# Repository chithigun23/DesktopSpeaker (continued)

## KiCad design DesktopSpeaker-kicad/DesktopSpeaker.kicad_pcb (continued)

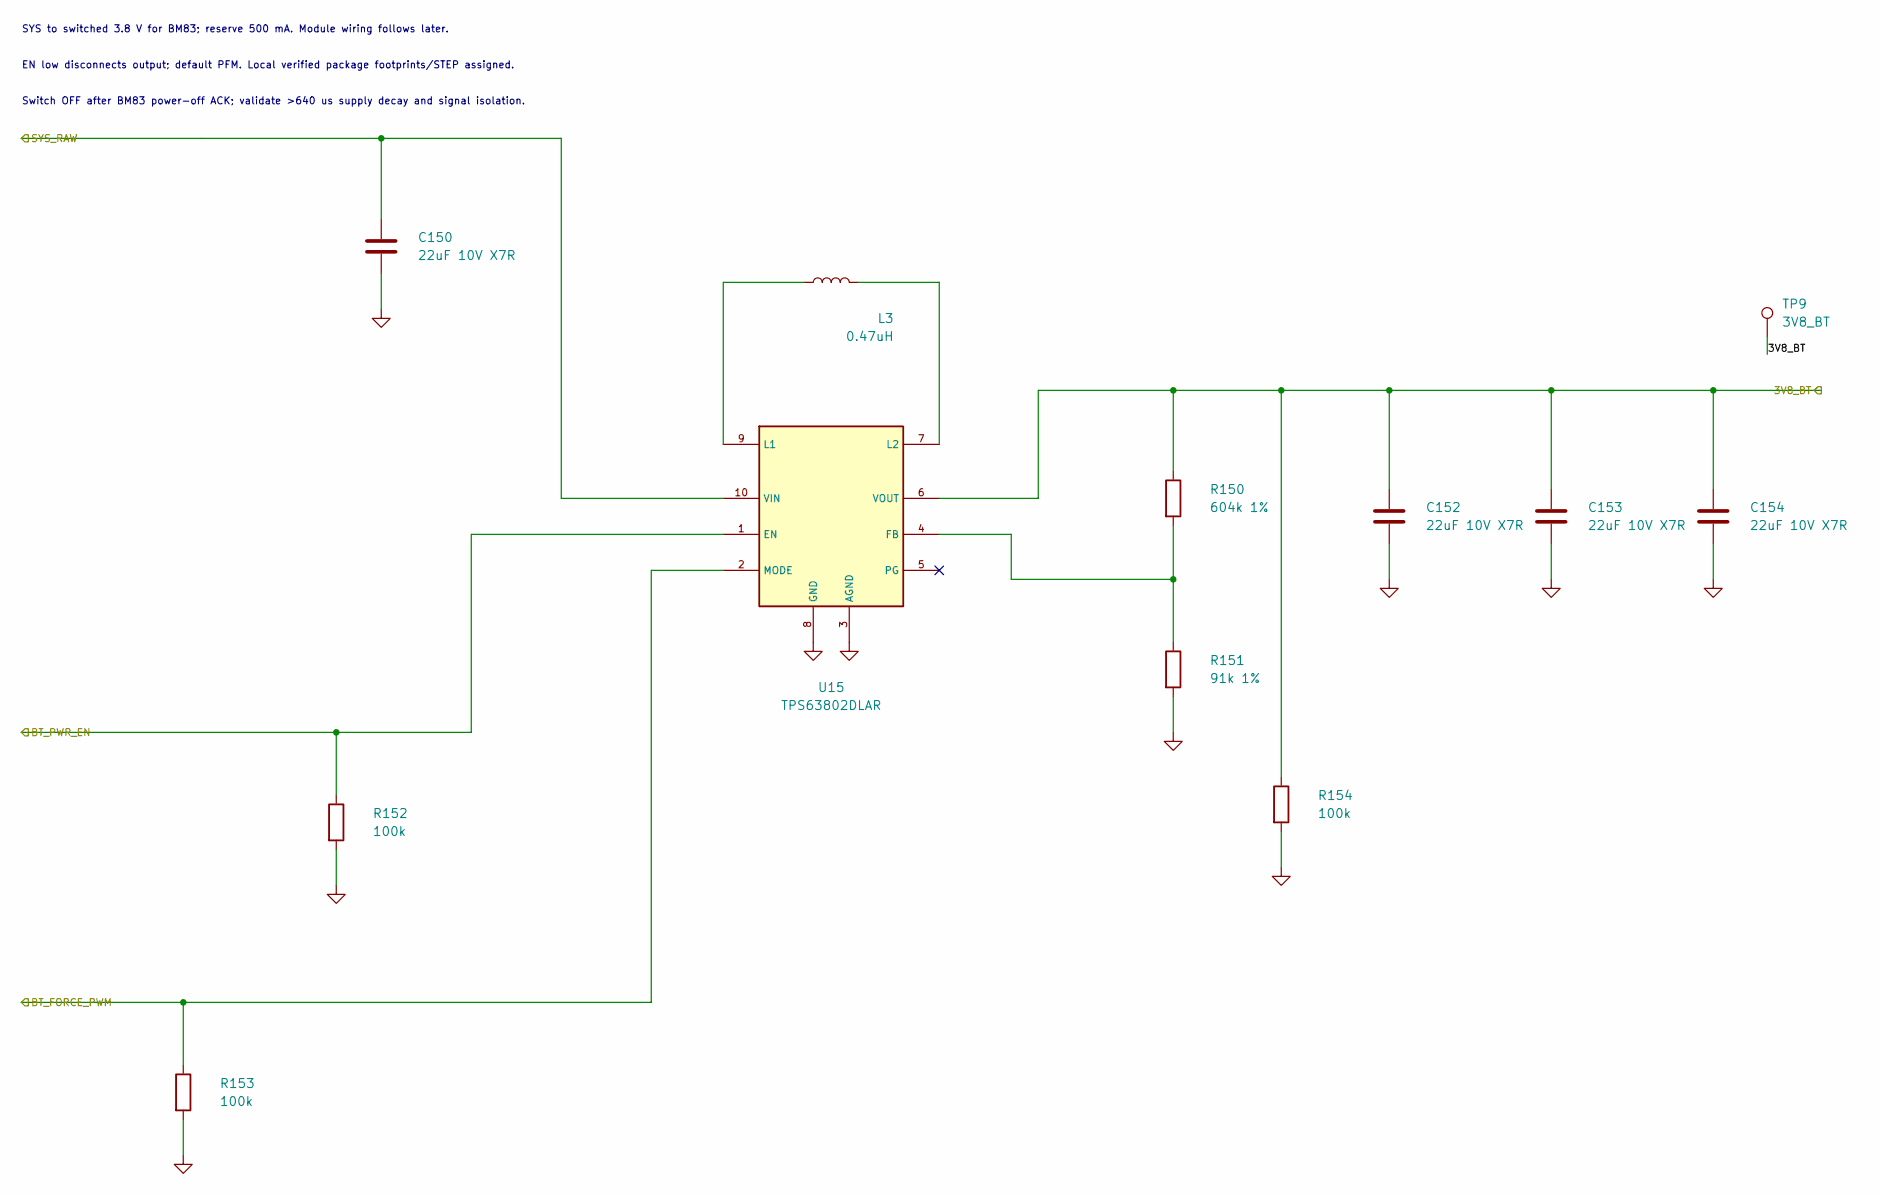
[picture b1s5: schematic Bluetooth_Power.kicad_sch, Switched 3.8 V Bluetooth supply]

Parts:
C150, C152, C153, C154: 22uF 10V X7R; C_0805_2012Metric_Pad1.18x1.45mm_HandSolder; MPN GRM21BZ71A226ME15L; LCSC C907991
L3: 0.47uH; Coilcraft_XFL4015-471MEC; MPN XFL4015-471MEC; LCSC Part C18221164
R150: 604k 1%; R_0402_1005Metric_Pad0.72x0.64mm_HandSolder; MPN 0402WGF6043TCE; LCSC C27013
R151: 91k 1%; R_0402_1005Metric_Pad0.72x0.64mm_HandSolder; MPN AC0402FR-0791KL; LCSC C144733
R152, R153, R154: 100k; R_0402_1005Metric_Pad0.72x0.64mm_HandSolder; MPN RC0402FR-07100KL; LCSC C60491
TP9: 3V8_BT; TestPoint_Keystone_5015_Micro_Mini
U15: TPS63802DLAR; MPN TPS63802DLAR; LCSC Part C2845237

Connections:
/3V8_BT: C152.1, C153.1, C154.1, R150.1, R154.1, TP9.1, U15.6 (VOUT); also elsewhere on the board
/BT_FORCE_PWM: R153.1, U15.2 (MODE); also elsewhere on the board
/BT_PWR_EN: R152.1, U15.1 (EN); also elsewhere on the board
/SYS_RAW: C150.1, U15.10 (VIN); also elsewhere on the board
GND: C150.2, C152.2, C153.2, C154.2, R151.2, R152.2, R153.2, R154.2, U15.3 (AGND), U15.8 (GND); also elsewhere on the board
unnamed: R150.2, R151.1, U15.4 (FB)
unnamed: L3.1, U15.9 (L1)
unnamed: L3.2, U15.7 (L2)

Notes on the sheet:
SYS to switched 3.8 V for BM83; reserve 500 mA. Module wiring follows later.
EN low disconnects output; default PFM. Local verified package footprints/STEP assigned.
Switch OFF after BM83 power-off ACK; validate >640 us supply decay and signal isolation.

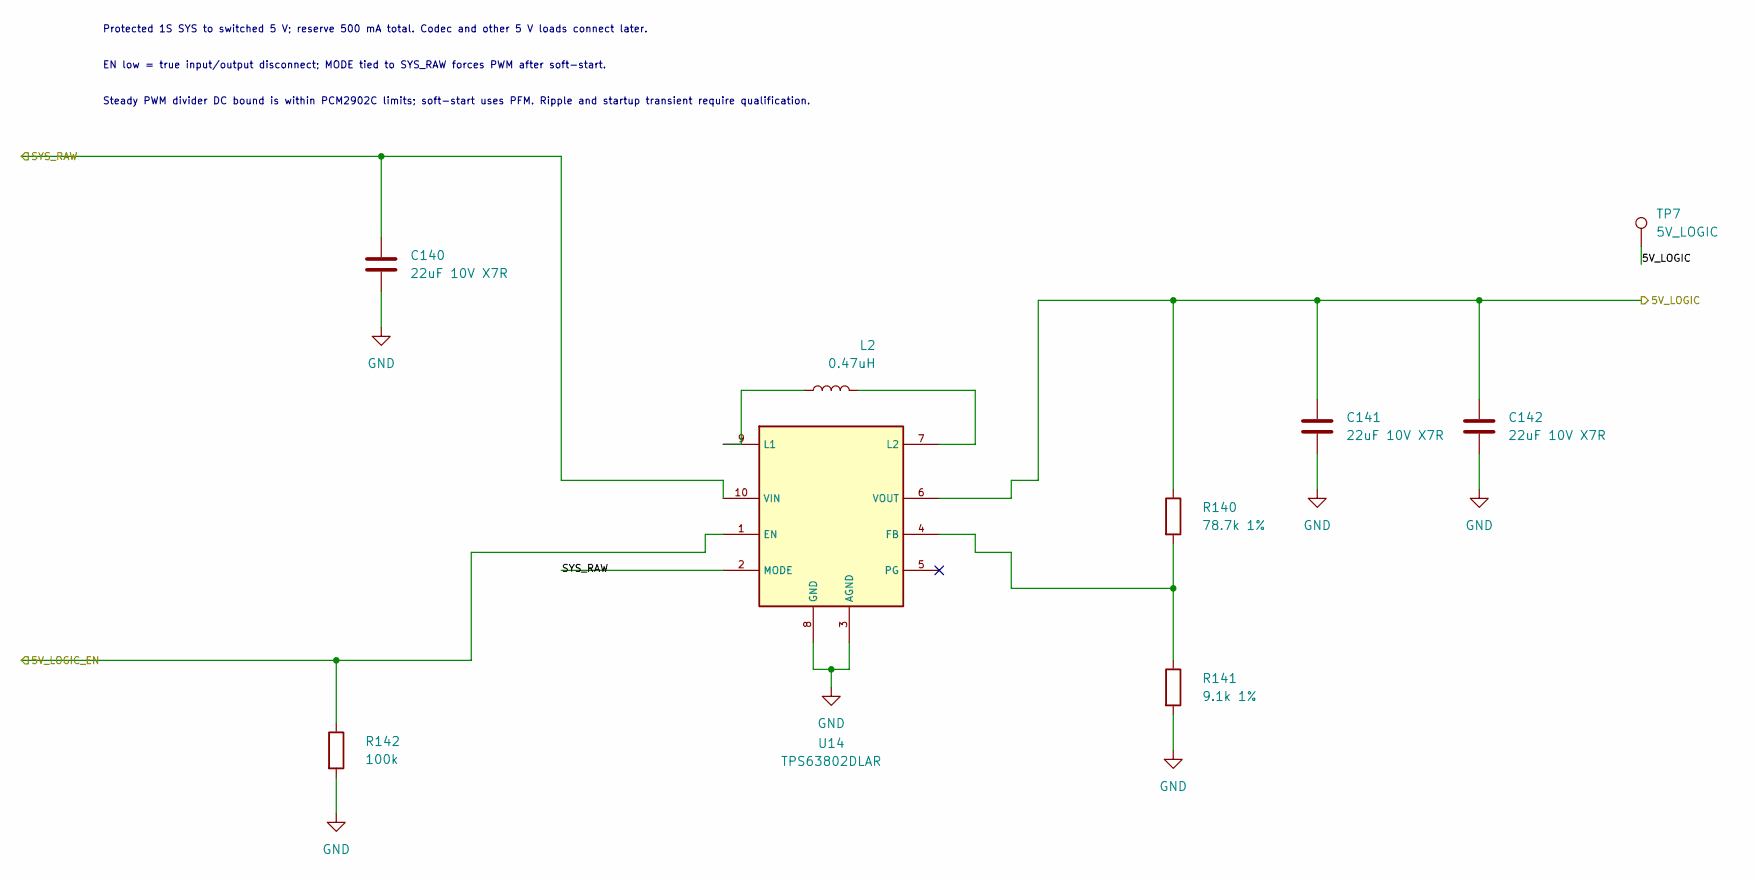
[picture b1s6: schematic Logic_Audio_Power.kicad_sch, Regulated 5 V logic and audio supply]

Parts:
C140, C141, C142: 22uF 10V X7R; C_0805_2012Metric_Pad1.18x1.45mm_HandSolder; MPN GRM21BZ71A226ME15L; LCSC C907991
L2: 0.47uH; Coilcraft_XFL4015-471MEC; MPN XFL4015-471MEC; LCSC Part C18221164
R140: 78.7k 1%; R_0402_1005Metric_Pad0.72x0.64mm_HandSolder; MPN RC0402FR-0778K7L; LCSC Part C163454
R141: 9.1k 1%; R_0402_1005Metric_Pad0.72x0.64mm_HandSolder; MPN RC0402FR-079K1L; LCSC Part C163450
R142: 100k; R_0402_1005Metric_Pad0.72x0.64mm_HandSolder; MPN RC0402FR-07100KL; LCSC Part C60491
TP7: 5V_LOGIC; TestPoint_Keystone_5015_Micro_Mini
U14: TPS63802DLAR; MPN TPS63802DLAR; LCSC Part C2845237

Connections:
/5V_LOGIC: C141.1, C142.1, R140.1, TP7.1, U14.6 (VOUT); also elsewhere on the board
/5V_LOGIC_EN: R142.1, U14.1 (EN); also elsewhere on the board
/SYS_RAW: C140.1, U14.2 (MODE), U14.10 (VIN); also elsewhere on the board
GND: C140.2, C141.2, C142.2, R141.2, R142.2, U14.3 (AGND), U14.8 (GND); also elsewhere on the board
unnamed: R140.2, R141.1, U14.4 (FB)
unnamed: L2.1, U14.9 (L1)
unnamed: L2.2, U14.7 (L2)

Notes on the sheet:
Protected 1S SYS to switched 5 V; reserve 500 mA total. Codec and other 5 V loads connect later.
EN low = true input/output disconnect; MODE tied to SYS_RAW forces PWM after soft-start.
Steady PWM divider DC bound is within PCM2902C limits; soft-start uses PFM. Ripple and startup transient require qualification.

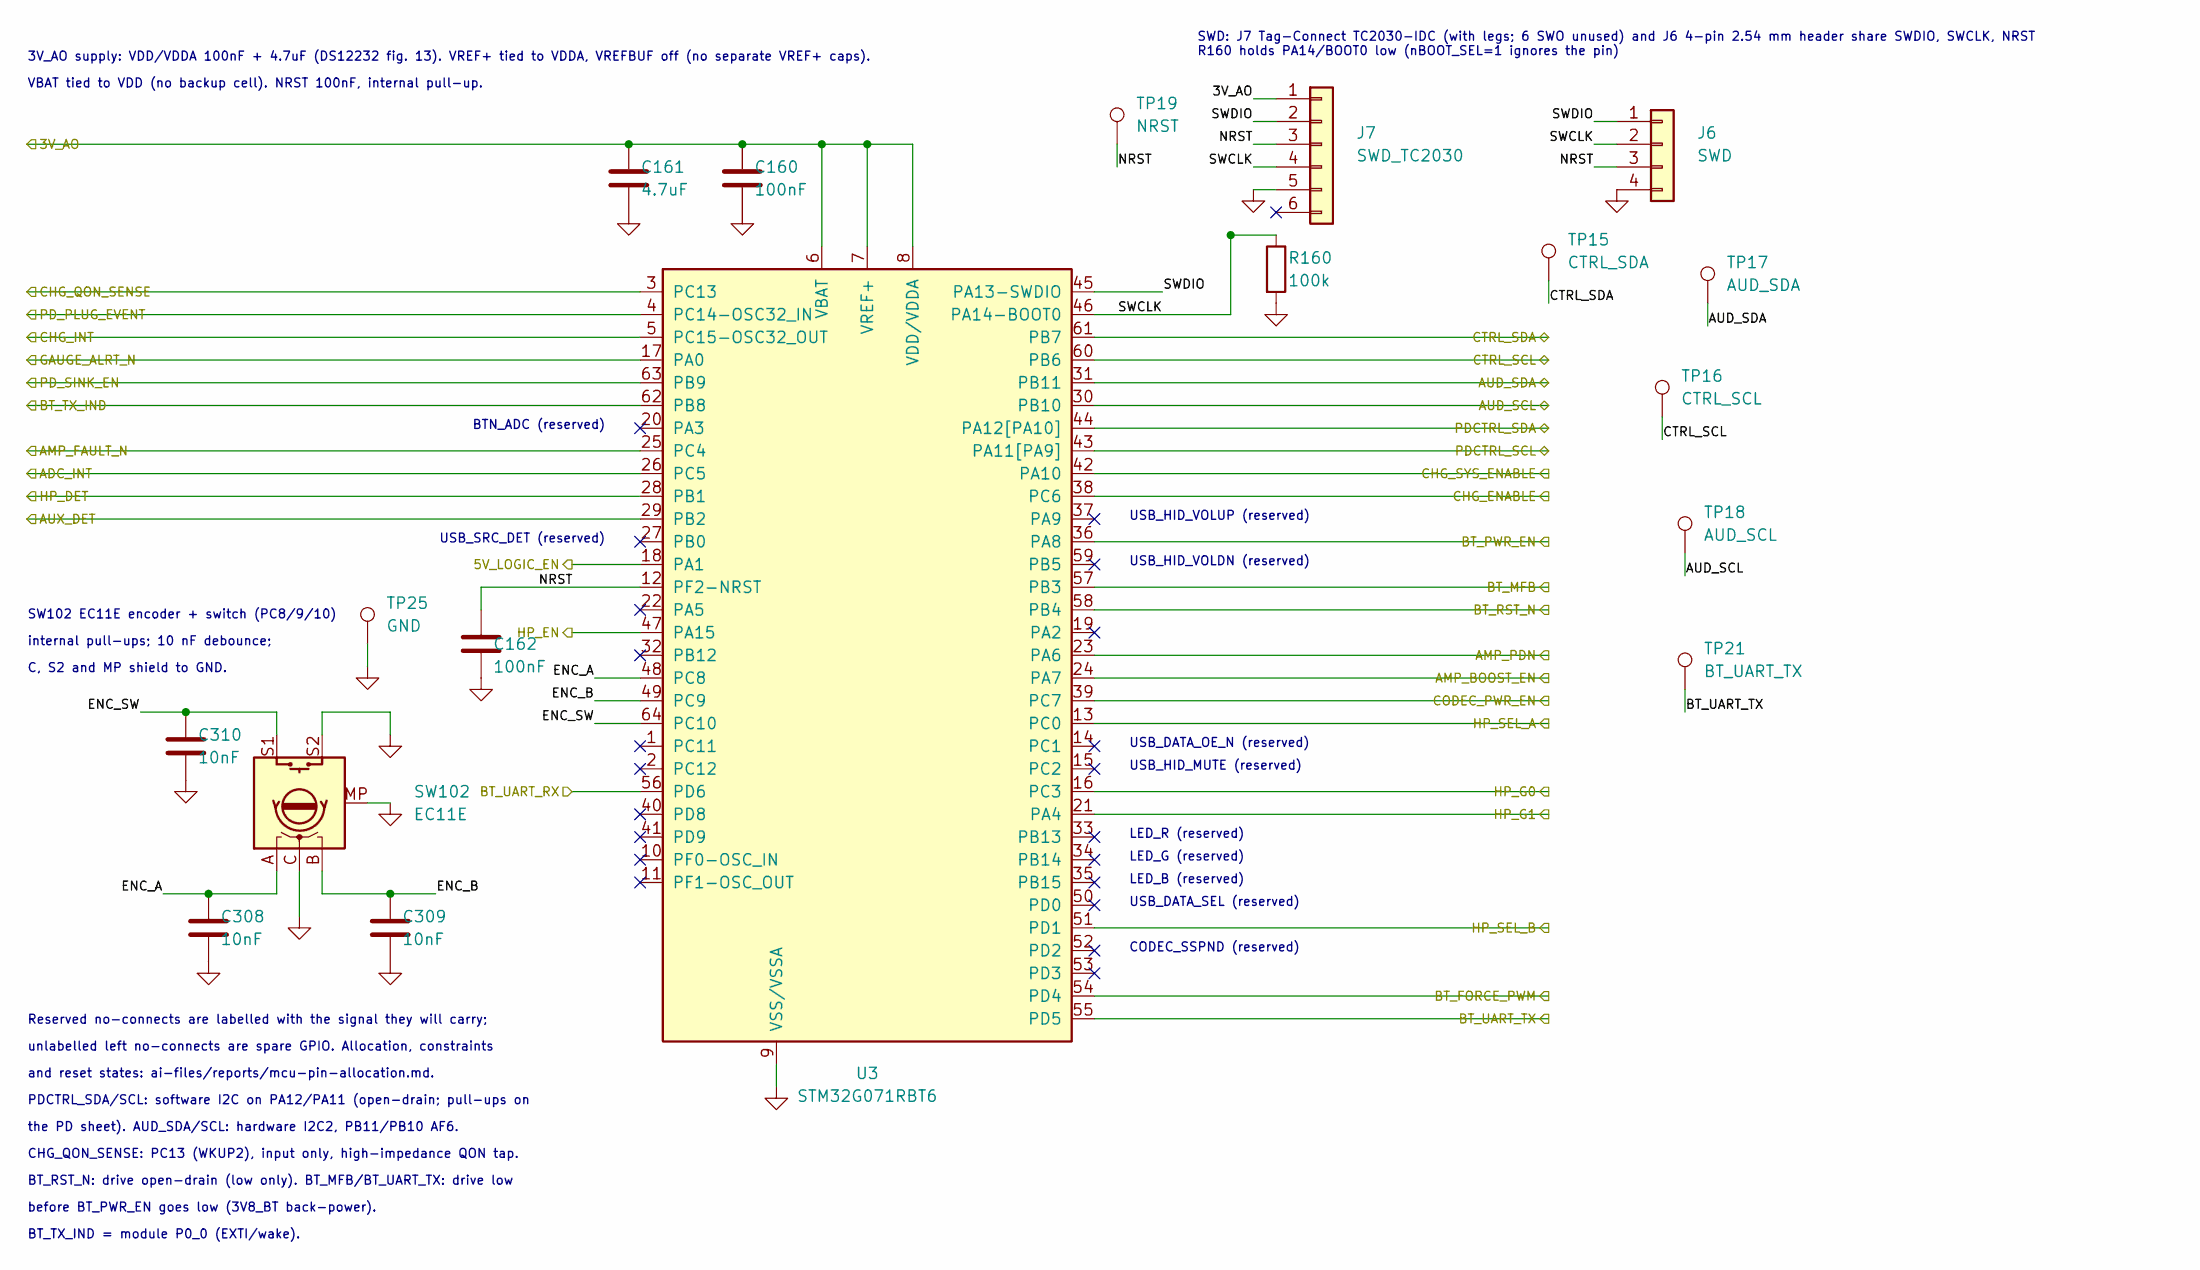
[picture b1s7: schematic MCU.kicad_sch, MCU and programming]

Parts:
C160, C162: 100nF; C_0402_1005Metric_Pad0.74x0.62mm_HandSolder; MPN GRM155R71H104KE14D; LCSC C77020
C161: 4.7uF; C_0805_2012Metric_Pad1.18x1.45mm_HandSolder; MPN CL21A475KAQNNNE; LCSC C1779
C308, C309, C310: 10nF; C_0402_1005Metric_Pad0.74x0.62mm_HandSolder; MPN GRM155R71H103KA88D; LCSC C77019
J6: SWD; PinHeader_1x04_P2.54mm_Vertical; MPN B-2100S04P-A110; LCSC C124378
J7: SWD_TC2030; Tag-Connect_TC2030-IDC-FP_2x03_P1.27mm_Vertical; MPN TC2030-IDC
R160: 100k; R_0402_1005Metric_Pad0.72x0.64mm_HandSolder; MPN RC0402FR-07100KL; LCSC C60491
SW102: EC11E; RotaryEncoder_Alps_EC11E-Switch_Vertical_H20mm_MountingHoles; MPN EC11E18244AU; LCSC C202365
TP15: CTRL_SDA; TestPoint_Keystone_5015_Micro_Mini
TP16: CTRL_SCL; TestPoint_Keystone_5015_Micro_Mini
TP17: AUD_SDA; TestPoint_Keystone_5015_Micro_Mini
TP18: AUD_SCL; TestPoint_Keystone_5015_Micro_Mini
TP19: NRST; TestPoint_Keystone_5015_Micro_Mini
TP21: BT_UART_TX; TestPoint_Keystone_5015_Micro_Mini
TP25: GND; TestPoint_Keystone_5010-5014_Multipurpose
U3: STM32G071RBT6; MPN STM32G071RBT6; LCSC Part C432213

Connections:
/3V_AO: C160.1, C161.1, J7.1, U3.6 (VBAT), U3.7 (VREF+), U3.8 (VDD/VDDA); also elsewhere on the board
/5V_LOGIC_EN: U3.18 (PA1); also elsewhere on the board
/ADC_INT: U3.26 (PC5); also elsewhere on the board
/AMP_BOOST_EN: U3.24 (PA7); also elsewhere on the board
/AMP_FAULT_N: U3.25 (PC4); also elsewhere on the board
/AMP_PDN: U3.23 (PA6); also elsewhere on the board
/AUD_SCL: TP18.1, U3.30 (PB10); also elsewhere on the board
/AUD_SDA: TP17.1, U3.31 (PB11); also elsewhere on the board
/AUX_DET: U3.29 (PB2); also elsewhere on the board
/BT_FORCE_PWM: U3.54 (PD4); also elsewhere on the board
/BT_MFB: U3.57 (PB3); also elsewhere on the board
/BT_PWR_EN: U3.36 (PA8); also elsewhere on the board
/BT_RST_N: U3.58 (PB4); also elsewhere on the board
/BT_TX_IND: U3.62 (PB8); also elsewhere on the board
/BT_UART_RX: U3.56 (PD6); also elsewhere on the board
/BT_UART_TX: TP21.1, U3.55 (PD5); also elsewhere on the board
/CHG_ENABLE: U3.38 (PC6); also elsewhere on the board
/CHG_INT: U3.5 (PC15-OSC32_OUT); also elsewhere on the board
/CHG_QON_SENSE: U3.3 (PC13); also elsewhere on the board
/CHG_SYS_ENABLE: U3.42 (PA10); also elsewhere on the board
/CODEC_PWR_EN: U3.39 (PC7); also elsewhere on the board
/CTRL_SCL: TP16.1, U3.60 (PB6); also elsewhere on the board
/CTRL_SDA: TP15.1, U3.61 (PB7); also elsewhere on the board
/GAUGE_ALRT_N: U3.17 (PA0); also elsewhere on the board
/HP_DET: U3.28 (PB1); also elsewhere on the board
/HP_EN: U3.47 (PA15); also elsewhere on the board
/HP_G0: U3.16 (PC3); also elsewhere on the board
/HP_G1: U3.21 (PA4); also elsewhere on the board
/HP_SEL_A: U3.13 (PC0); also elsewhere on the board
/HP_SEL_B: U3.51 (PD1); also elsewhere on the board
/MCU/ENC_A: C308.1, SW102.A, U3.48 (PC8)
/MCU/ENC_B: C309.1, SW102.B, U3.49 (PC9)
/MCU/ENC_SW: C310.1, SW102.S1, U3.64 (PC10)
/MCU/NRST: C162.1, J6.3, J7.3, TP19.1, U3.12 (PF2-NRST)
/MCU/SWCLK: J6.2, J7.4, R160.1, U3.46 (PA14-BOOT0)
/MCU/SWDIO: J6.1, J7.2, U3.45 (PA13-SWDIO)
/PDCTRL_SCL: U3.43 (PA11[PA9]); also elsewhere on the board
/PDCTRL_SDA: U3.44 (PA12[PA10]); also elsewhere on the board
/PD_PLUG_EVENT: U3.4 (PC14-OSC32_IN); also elsewhere on the board
/PD_SINK_EN: U3.63 (PB9); also elsewhere on the board
GND: C160.2, C161.2, C162.2, C308.2, C309.2, C310.2, J6.4, J7.5, R160.2, SW102.C, SW102.MP, SW102.S2, TP25.1, U3.9 (VSS/VSSA); also elsewhere on the board

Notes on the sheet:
SWD: J7 Tag-Connect TC2030-IDC (with legs; 6 SWO unused) and J6 4-pin 2.54 mm header share SWDIO, SWCLK, NRST R160 holds PA14/BOOT0 low (nBOOT_SEL=1 ignores the pin)
USB_SRC_DET (reserved)
BTN_ADC (reserved)
LED_R (reserved)
LED_G (reserved)
LED_B (reserved)
USB_DATA_SEL (reserved)
USB_DATA_OE_N (reserved)
CODEC_SSPND (reserved)
USB_HID_MUTE (reserved)
USB_HID_VOLUP (reserved)
USB_HID_VOLDN (reserved)
3V_AO supply: VDD/VDDA 100nF + 4.7uF (DS12232 fig. 13). VREF+ tied to VDDA, VREFBUF off (no separate VREF+ caps).
VBAT tied to VDD (no backup cell). NRST 100nF, internal pull-up.
Reserved no-connects are labelled with the signal they will carry;
unlabelled left no-connects are spare GPIO. Allocation, constraints
and reset states: ai-files/reports/mcu-pin-allocation.md.
PDCTRL_SDA/SCL: software I2C on PA12/PA11 (open-drain; pull-ups on
the PD sheet). AUD_SDA/SCL: hardware I2C2, PB11/PB10 AF6.
CHG_QON_SENSE: PC13 (WKUP2), input only, high-impedance QON tap.
BT_RST_N: drive open-drain (low only). BT_MFB/BT_UART_TX: drive low
before BT_PWR_EN goes low (3V8_BT back-power).
BT_TX_IND = module P0_0 (EXTI/wake).
SW102 EC11E encoder + switch (PC8/9/10)
internal pull-ups; 10 nF debounce;
C, S2 and MP shield to GND.

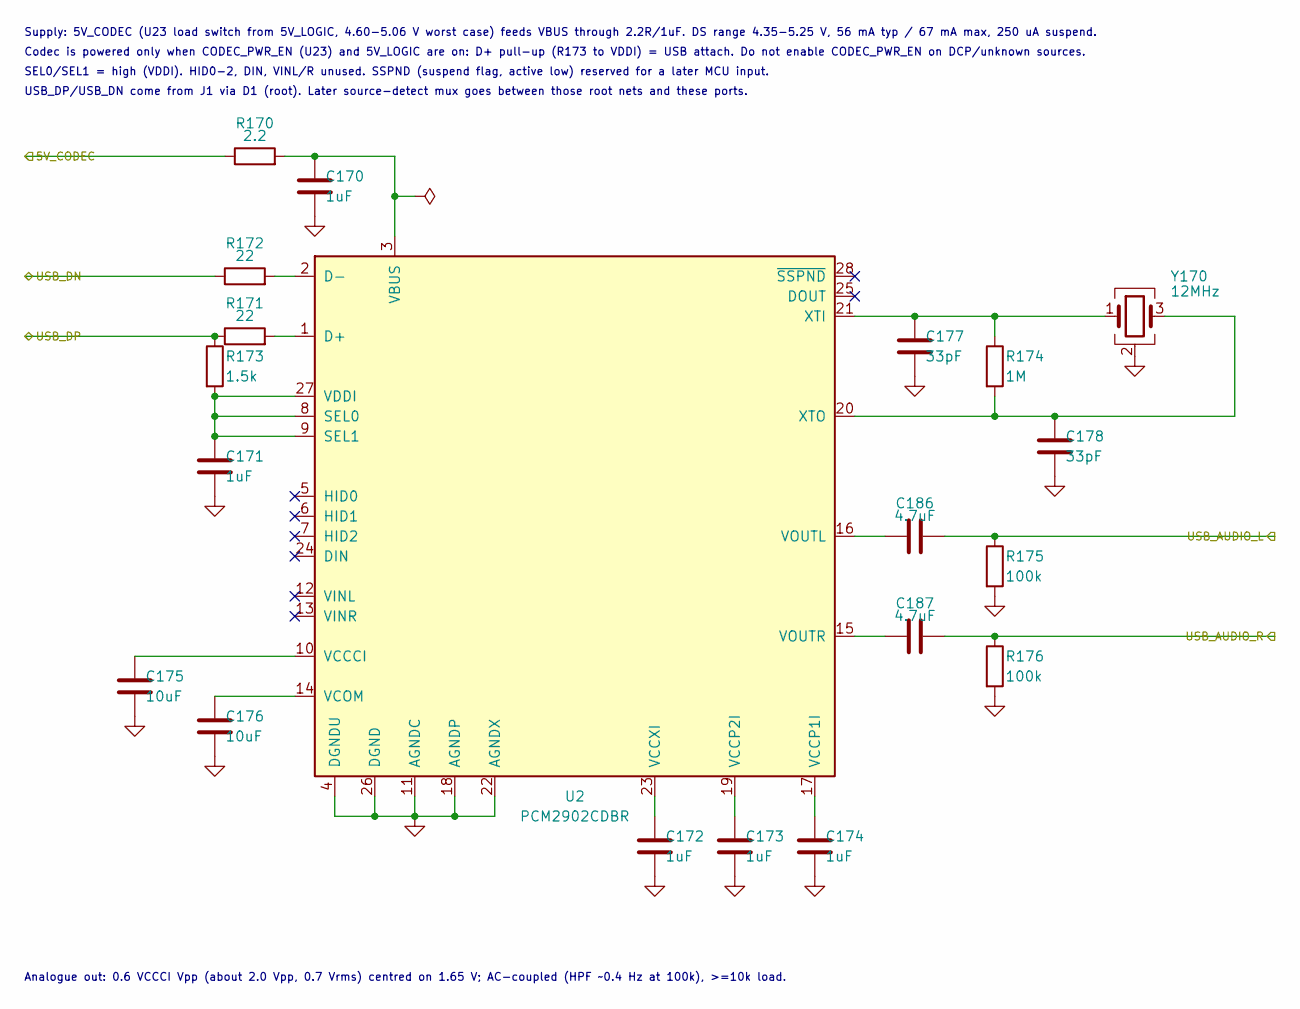
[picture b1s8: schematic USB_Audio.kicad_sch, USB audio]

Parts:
C170, C171, C172, C173, C174: 1uF; C_0402_1005Metric_Pad0.74x0.62mm_HandSolder; MPN CL05A105KO5NNNC; LCSC C29266
C175, C176: 10uF; C_0805_2012Metric_Pad1.18x1.45mm_HandSolder; MPN CL21B106KPQNNNE; LCSC C32635
C177, C178: 33pF; C_0402_1005Metric_Pad0.74x0.62mm_HandSolder; MPN FCC0402N330J500AT; LCSC C5137486
C186, C187: 4.7uF; C_0805_2012Metric_Pad1.18x1.45mm_HandSolder; MPN CL21A475KAQNNNE; LCSC C1779
R170: 2.2; R_0402_1005Metric_Pad0.72x0.64mm_HandSolder; MPN RC0402FR-072R2L; LCSC C327251
R171, R172: 22; R_0402_1005Metric_Pad0.72x0.64mm_HandSolder; MPN RC0402FR-0722RL; LCSC C114765
R173: 1.5k; R_0402_1005Metric_Pad0.72x0.64mm_HandSolder; MPN RC0402FR-071K5L; LCSC C114759
R174: 1M; R_0402_1005Metric_Pad0.72x0.64mm_HandSolder; MPN RC0402FR-071ML; LCSC C138033
R175, R176: 100k; R_0402_1005Metric_Pad0.72x0.64mm_HandSolder; MPN RC0402FR-07100KL; LCSC C60491
U2: PCM2902CDBR; MPN PCM2902CDBR; LCSC Part C2651869
Y170: 12MHz; Crystal_SMD_3225-4Pin_3.2x2.5mm; MPN K3A120002010; LCSC C368730

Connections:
/5V_CODEC: R170.1; also elsewhere on the board
/USB_AUDIO_L: C186.2, R175.1; also elsewhere on the board
/USB_AUDIO_R: C187.2, R176.1; also elsewhere on the board
/USB_DN: R172.1; also elsewhere on the board
/USB_DP: R171.1, R173.1; also elsewhere on the board
GND: C170.2, C171.2, C172.2, C173.2, C174.2, C175.2, C176.2, C177.2, C178.2, R175.2, R176.2, U2.4 (DGNDU), U2.11 (AGNDC), U2.18 (AGNDP), U2.22 (AGNDX), U2.26 (DGND), Y170.2 (G), Y170.4 (G); also elsewhere on the board
unnamed: R171.2, U2.1 (D+)
unnamed: R172.2, U2.2 (D-)
unnamed: C171.1, R173.2, U2.8 (SEL0), U2.9 (SEL1), U2.27 (VDDI)
unnamed: C170.1, R170.2, U2.3 (VBUS)
unnamed: C175.1, U2.10 (VCCCI)
unnamed: C174.1, U2.17 (VCCP1I)
unnamed: C173.1, U2.19 (VCCP2I)
unnamed: C172.1, U2.23 (VCCXI)
unnamed: C176.1, U2.14 (VCOM)
unnamed: C186.1, U2.16 (VOUTL)
unnamed: C187.1, U2.15 (VOUTR)
unnamed: C177.1, R174.1, U2.21 (XTI), Y170.1
unnamed: C178.1, R174.2, U2.20 (XTO), Y170.3

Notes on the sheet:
Supply: 5V_CODEC (U23 load switch from 5V_LOGIC, 4.60-5.06 V worst case) feeds VBUS through 2.2R/1uF. DS range 4.35-5.25 V, 56 mA typ / 67 mA max, 250 uA suspend.
Codec is powered only when CODEC_PWR_EN (U23) and 5V_LOGIC are on: D+ pull-up (R173 to VDDI) = USB attach. Do not enable CODEC_PWR_EN on DCP/unknown sources.
SEL0/SEL1 = high (VDDI). HID0-2, DIN, VINL/R unused. SSPND (suspend flag, active low) reserved for a later MCU input.
USB_DP/USB_DN come from J1 via D1 (root). Later source-detect mux goes between those root nets and these ports.
Analogue out: 0.6 VCCCI Vpp (about 2.0 Vpp, 0.7 Vrms) centred on 1.65 V; AC-coupled (HPF ~0.4 Hz at 100k), >=10k load.

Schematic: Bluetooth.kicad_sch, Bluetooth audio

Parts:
C190: 10uF; C_0805_2012Metric_Pad1.18x1.45mm_HandSolder; MPN CL21B106KPQNNNE; LCSC C32635
C191: 100nF; C_0402_1005Metric_Pad0.74x0.62mm_HandSolder; MPN GRM155R71H104KE14D; LCSC C77020
C192, C193: 1uF; C_0402_1005Metric_Pad0.74x0.62mm_HandSolder; MPN CL05A105KO5NNNC; LCSC C29266
C194, C195: 4.7uF; C_0805_2012Metric_Pad1.18x1.45mm_HandSolder; MPN CL21A475KAQNNNE
J8: BM83_PROG; PinHeader_1x05_P2.54mm_Vertical; MPN XY-MTP254-1X5; LCSC C54110162
R180, R181, R184: 100k; R_0402_1005Metric_Pad0.72x0.64mm_HandSolder; MPN RC0402FR-07100KL; LCSC C60491
R182, R183: 10k; R_0402_1005Metric_Pad0.72x0.64mm_HandSolder; MPN RC0402FR-0710KL; LCSC C60490
R185, R186, R187: 1k; R_0402_1005Metric_Pad0.72x0.64mm_HandSolder; MPN RC0402FR-071KL
TP22: BT_UART_RX; TestPoint_Keystone_5015_Micro_Mini
U1: BM83SM1-00TA; MPN BM83SM1-00TA; LCSC Part C6752723

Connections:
/3V8_BT: C190.1, C191.1, U1.23 (BAT_IN); also elsewhere on the board
/BT_AUDIO_L: C194.2, R180.1; also elsewhere on the board
/BT_AUDIO_R: C195.2, R181.1; also elsewhere on the board
/BT_MFB: R183.1; also elsewhere on the board
/BT_RST_N: R185.1; also elsewhere on the board
/BT_TX_IND: R187.2; also elsewhere on the board
/BT_UART_RX: R186.2, TP22.1; also elsewhere on the board
/BT_UART_TX: R182.1; also elsewhere on the board
/Bluetooth/BT_RST_M: J8.1, R185.2, U1.43 (RST_N)
/Bluetooth/BT_RXD_M: J8.3, R182.2, U1.29 (P8_6/UART_RXD)
/Bluetooth/BT_SYS_CFG: J8.2, U1.31 (P3_4/UART_RTS)
/Bluetooth/BT_TXD_M: J8.4, R186.1, U1.30 (P8_5/UART_TXD)
GND: C190.2, C191.2, C192.2, C193.2, J8.5, R180.2, R181.2, R184.2, U1.16, U1.50, U1.56, U1.57, U1.[16,50,56,57] (GND); also elsewhere on the board
unnamed: C194.1, U1.8 (AOHPL)
unnamed: C195.1, U1.6 (AOHPR)
unnamed: R187.1, U1.49 (P0_0/UART_TX_IND)
unnamed: R183.2, R184.1, U1.26 (PWR(MFB))
unnamed: C193.1, U1.24 (SYS_PWR)
unnamed: C192.1, U1.25 (VDD_IO)

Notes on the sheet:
BM83SM1-00TA (DS70005402D). BAT_IN 3.2-4.2 V from 3V8_BT (U15); SYS_PWR/VDD_IO are outputs (decoupling only, do not load or feed). ADAP_IN unused (internal charger/USB DFU not used).
Host mode UART from the MCU: P8_6 RXD / P8_5 TXD, P0_0 = UART_TX_IND (wakes the MCU). MFB (PWR) = power-on/wake key, RST_N = reset (active low, internal pull-up). Config Tool must set Host mode, P0_0 as TX_IND.
Back-power: MCU lines pass 10k/1k series resistors; firmware must drive PA2/PB3 low (PB4 open-drain/hi-Z) and disable BT_PWR_EN only after the module power-off ACK. Module outputs are 3.0-3.6 V into 5 V tolerant MCU pins.
Audio: single-ended DAC out (AOHPL/AOHPR) AC-coupled, 4.7 uF + 100k bleed, 0.74 Vrms full scale; AOHPM (capless sense) unused. Ports feed the later source-select sheet.
Antenna: integrated PCB antenna, no external RF parts. Keep the antenna end of the module off the board (no copper/components/keep-out) and metal 15 mm clear; see ai-files/reports/bluetooth-notes.md.
J8 programming/test (isUpdate/Config Tool): 1 RST_N, 2 P3_4 SYS_CFG (low at reset = test mode), 3 UART_RXD (adapter TX), 4 UART_TXD (adapter RX), 5 GND. 3V8_BT must be enabled first.

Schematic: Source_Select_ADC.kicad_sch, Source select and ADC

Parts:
C200, C201, C202, C203, C204, C205: 2.2uF; C_0402_1005Metric_Pad0.74x0.62mm_HandSolder; MPN CL05A225KP5NNNC; LCSC C7464343
C206, C207, C208, C209, C210, C211: 10nF C0G; C_0402_1005Metric_Pad0.74x0.62mm_HandSolder; MPN GRM1555C1H103JE01D; LCSC C22400107
C212, C220, C221, C222, C224, C225: 1uF; C_0402_1005Metric_Pad0.74x0.62mm_HandSolder; MPN CL05A105KO5NNNC; LCSC C29266
C213, C215, C217, C219: 100nF; C_0402_1005Metric_Pad0.74x0.62mm_HandSolder; MPN GRM155R71H104KE14D; LCSC C77020
C214, C216, C218, C223: 10uF; C_0805_2012Metric_Pad1.18x1.45mm_HandSolder; MPN CL21B106KPQNNNE; LCSC C32635
C226, C227: 15pF C0G; C_0402_1005Metric_Pad0.74x0.62mm_HandSolder; MPN GRM1555C1H150JA01D; LCSC C76950
FB200: BLM15AG601SN1D; R_0402_1005Metric_Pad0.72x0.64mm_HandSolder; MPN BLM15AG601SN1D; LCSC C76884
R200, R201, R202, R203, R204, R205: 100; R_0402_1005Metric_Pad0.72x0.64mm_HandSolder; MPN RC0402FR-07100RL; LCSC C106232
R206, R207, R208: 33; R_0402_1005Metric_Pad0.72x0.64mm_HandSolder; MPN RC0402FR-0733RL; LCSC C138002
R209, R210: 2.2k; R_0402_1005Metric_Pad0.72x0.64mm_HandSolder; MPN RC0402FR-072K2L; LCSC C114762
R211, R212: 100k; R_0402_1005Metric_Pad0.72x0.64mm_HandSolder; MPN RC0402FR-07100KL; LCSC C60491
TP6: 3V3_AUDIO; TestPoint_Keystone_5015_Micro_Mini
TP8: 5V_CODEC; TestPoint_Keystone_5015_Micro_Mini
TP12: I2S_BCK; TestPoint_Keystone_5015_Micro_Mini
TP13: I2S_SDATA; TestPoint_Keystone_5015_Micro_Mini
TP14: I2S_LRCK; TestPoint_Keystone_5015_Micro_Mini
U22: TPS7A2033PDBVR; MPN TPS7A2033PDBVR; LCSC Part C2862740
U23: TPS22917DBVR; MPN TPS22917DBVR; LCSC Part C2681320
U24: PCM1862DBTR; MPN PCM1862DBTR; LCSC Part C544647
Y200: 24.576MHz; Crystal_SMD_3225-4Pin_3.2x2.5mm; MPN X322524576MOB4SI; LCSC C70568

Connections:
/3V3_AUDIO: C217.1, C218.1, C219.1, C220.1, C222.1, C223.1, FB200.1, R209.1, R210.1, TP6.1, U22.5 (OUT), U24.13 (DVDD), U24.14 (IOVDD); also elsewhere on the board
/5V_CODEC: C225.1, TP8.1, U23.5 (QOD), U23.6 (VOUT); also elsewhere on the board
/5V_LOGIC: C221.1, C224.1, U22.1 (IN), U22.3 (EN), U23.1 (VIN); also elsewhere on the board
/ADC_INT: R211.1, U24.21 (GPIO1/INTA); also elsewhere on the board
/AUD_SCL: R209.2, U24.24 (MC/SCL); also elsewhere on the board
/AUD_SDA: R210.2, U24.23 (MOSI/SDA); also elsewhere on the board
/AUX_L: C204.1; also elsewhere on the board
/AUX_R: C205.1; also elsewhere on the board
/BT_AUDIO_L: C202.1; also elsewhere on the board
/BT_AUDIO_R: C203.1; also elsewhere on the board
/CODEC_PWR_EN: R212.1, U23.3 (ON); also elsewhere on the board
/I2S_BCK: R207.2, TP12.1; also elsewhere on the board
/I2S_LRCK: R208.2, TP14.1; also elsewhere on the board
/I2S_SDATA: R206.2, TP13.1; also elsewhere on the board
/USB_AUDIO_L: C200.1; also elsewhere on the board
/USB_AUDIO_R: C201.1; also elsewhere on the board
GND: C206.2, C207.2, C208.2, C209.2, C210.2, C211.2, C212.2, C213.2, C214.2, C215.2, C216.2, C217.2, C218.2, C219.2, C220.2, C221.2, C222.2, C223.2, C224.2, C225.2, C226.2, C227.2, R211.2, R212.2, U22.2 (GND), U23.2 (GND), U24.7 (AGND), U24.12 (DGND), U24.15 (SCKI), U24.25 (MS/AD), U24.26 (MD0), Y200.2 (G), Y200.4 (G); also elsewhere on the board
unnamed: C200.2, R200.1
unnamed: C201.2, R201.1
unnamed: C202.2, R202.1
unnamed: C203.2, R203.1
unnamed: C204.2, R204.1
unnamed: C205.2, R205.1
unnamed: C215.1, C216.1, FB200.2, U24.8 (AVDD)
unnamed: R207.1, U24.17 (BCK)
unnamed: R206.1, U24.18 (DOUT)
unnamed: C213.1, C214.1, U24.11 (LDO)
unnamed: R208.1, U24.16 (LRCK)
unnamed: C206.1, R200.2, U24.3 (VINL1)
unnamed: C208.1, R202.2, U24.1 (VINL2)
unnamed: C210.1, R204.2, U24.29 (VINL3)
unnamed: C207.1, R201.2, U24.4 (VINR1)
unnamed: C209.1, R203.2, U24.2 (VINR2)
unnamed: C211.1, R205.2, U24.30 (VINR3)
unnamed: C212.1, U24.6 (VREF)
unnamed: C226.1, U24.10 (XI), Y200.1
unnamed: C227.1, U24.9 (XO), Y200.3

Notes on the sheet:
Power: U22 TPS7A2033 (3V3_AUDIO, EN tied to IN) and U23 TPS22917 (5V_CODEC for USB_Audio, CODEC_PWR_EN, QOD tied to VOUT, CT open).
PCM1862: I2C mode (MD0 low), address 0x4A (MS/AD low), I2S master from the 24.576 MHz crystal (512 fs, PLL off), SCKI grounded. VIN1 = USB, VIN2 = BT, VIN3 = AUX.
Inputs: 2.2 uF - 100 R - 10 nF C0G (datasheet fig. 61 filter; ~5 mA ESD-diode limit). AVDD via FB200. No reset pin: firmware re-initialises after every 3V3_AUDIO enable.
Crystal CL 15 pF (Lucki L327S240P11L): 2 x 22 pF with about 3 pF stray gives about 14 pF; trim at bring-up. Spare VIN4, MICBIAS and GPIO0/2/3 are no-connect.

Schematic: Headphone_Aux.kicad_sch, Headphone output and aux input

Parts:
C230, C231, C232, C233, C234, C235, C239, C240, C245: 1uF; C_0402_1005Metric_Pad0.74x0.62mm_HandSolder; MPN CL05A105KO5NNNC; LCSC C29266
C236: 4.7uF; C_0805_2012Metric_Pad1.18x1.45mm_HandSolder; MPN CL21A475KAQNNNE
C237, C238, C246: 100nF; C_0402_1005Metric_Pad0.74x0.62mm_HandSolder; MPN GRM155R71H104KE14D; LCSC C77020
C241, C243, C244: 2.2uF; C_0402_1005Metric_Pad0.74x0.62mm_HandSolder; MPN CL05A225KP5NNNC
D200, D201: PESD5V0S2BT; MPN PESD5V0S2BT; LCSC Part C5380400
J2: HEAD_OUT; PJ-307; MPN PJ-307; LCSC Part C2939173
J3: AUX_IN; PJ-307; MPN PJ-307; LCSC Part C2939173
R220, R221, R222, R223, R224, R225, R234, R235, R236, R237, R238, R239: 100k; R_0402_1005Metric_Pad0.72x0.64mm_HandSolder; MPN RC0402FR-07100KL; LCSC C60491
R226, R227, R228, R229, R230, R231, R240: 1k; R_0402_1005Metric_Pad0.72x0.64mm_HandSolder; MPN RC0402FR-071KL
R232, R233: 47k; R_0402_1005Metric_Pad0.72x0.64mm_HandSolder; MPN RC0402FR-0747KL
R241: 1M; R_0402_1005Metric_Pad0.72x0.64mm_HandSolder; MPN RC0402FR-071ML
R242, R243, R244: 10k; R_0402_1005Metric_Pad0.72x0.64mm_HandSolder; MPN RC0402FR-0710KL; LCSC C60490
U8, U9: TS5A23157DGSR; MPN TS5A23157DGSR; LCSC Part C11133
U10: TPA6132A2RTER; MPN TPA6132A2RTER; LCSC Part C69901

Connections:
/3V3_AUDIO: C237.1, C238.1, C241.1, R232.1, R239.1, U8.8 (V+), U9.8 (V+), U10.14 (VDD); also elsewhere on the board
/3V_AO: R241.1; also elsewhere on the board
/AUX_DET: R242.2; also elsewhere on the board
/AUX_L: C234.1, D201.1, J3.5 (TIP), R243.1; also elsewhere on the board
/AUX_R: C235.1, D201.2, J3.2 (RING), R244.1; also elsewhere on the board
/BT_AUDIO_L: C232.1; also elsewhere on the board
/BT_AUDIO_R: C233.1; also elsewhere on the board
/HP_DET: R240.2; also elsewhere on the board
/HP_EN: R236.1, U10.13 (EN); also elsewhere on the board
/HP_G0: R237.1, U10.6 (G0); also elsewhere on the board
/HP_G1: R238.1, U10.7 (G1); also elsewhere on the board
/HP_SEL_A: R234.1, U8.1 (IN1), U8.5 (IN2); also elsewhere on the board
/HP_SEL_B: R235.1, U9.1 (IN1), U9.5 (IN2); also elsewhere on the board
/Headphone_Aux/AUX_TIPSW: C246.1, J3.4 (TIP_SW), R241.2, R242.1
/Headphone_Aux/HP_L: C239.1, U9.10 (COM1)
/Headphone_Aux/HP_OUTL: D200.1, J2.5 (TIP), U10.16 (OUTL)
/Headphone_Aux/HP_OUTR: D200.2, J2.2 (RING), U10.5 (OUTR)
/Headphone_Aux/HP_R: C240.1, U9.6 (COM2)
/Headphone_Aux/HP_TIPSW: J2.4 (TIP_SW), R239.2, R240.1
/Headphone_Aux/VMID_HP: C236.1, R220.2, R221.2, R222.2, R223.2, R224.2, R225.2, R232.2, R233.1
/USB_AUDIO_L: C230.1; also elsewhere on the board
/USB_AUDIO_R: C231.1; also elsewhere on the board
GND: C236.2, C237.2, C238.2, C241.2, C243.2, C244.2, C246.2, D200.3, D201.3, J2.1 (SLEEVE), J3.1 (SLEEVE), R233.2, R234.2, R235.2, R236.2, R237.2, R238.2, R243.2, R244.2, U8.3 (GND), U9.3 (GND), U10.2, U10.3, U10.10, U10.15 (SGND), U10.17, U10.[2,3,10,17] (GND); also elsewhere on the board
unnamed: C230.2, R220.1, R226.1
unnamed: C231.2, R221.1, R227.1
unnamed: C232.2, R222.1, R228.1
unnamed: C233.2, R223.1, R229.1
unnamed: C234.2, R224.1, R230.1
unnamed: C235.2, R225.1, R231.1
unnamed: U8.10 (COM1), U9.9 (NC1)
unnamed: U8.6 (COM2), U9.7 (NC2)
unnamed: R226.2, U8.9 (NC1)
unnamed: R227.2, U8.7 (NC2)
unnamed: R228.2, U8.2 (NO1)
unnamed: R229.2, U8.4 (NO2)
unnamed: R230.2, U9.2 (NO1)
unnamed: R231.2, U9.4 (NO2)
unnamed: C245.2, U10.9 (CPN)
unnamed: C245.1, U10.11 (CPP)
unnamed: C243.1, U10.12 (HPVDD)
unnamed: C244.1, U10.8 (HPVSS)
unnamed: C239.2, U10.1 (INL-)
unnamed: C240.2, U10.4 (INR-)

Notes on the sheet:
Mux: USB (default), BT, AUX select by HP_SEL_B/HP_SEL_A = 00 / 01 / 1x. HP_SEL_A,B, HP_EN, HP_G0/G1 default low (pull-downs): USB, amp off, -6 dB.
Sequence: HP_EN low, change HP_SEL, wait 1 ms, HP_EN high (5 ms start-up). Hold HP_EN, HP_G0, HP_G1 low while 3V3_AUDIO is off.
Inputs: 1 uF AC coupling, 100 k bias to VMID_HP (1.65 V from 3V3_AUDIO), 1 k series. TPA6132A2 inputs are single-ended (INL+/INR+ grounded).
J2 switched tip (4) = HP_DET (low without plug, high with plug). J3 switched tip (4) = AUX_DET. Switched ring (3): not connected. No hardware speaker mute: firmware mutes the speaker chain on insertion.
SGND (pin 15) goes to the J2 sleeve: route as its own trace to the jack sleeve ground, away from PGND. PESD5V0S2BT pin 3 = common: VERIFY against datasheet.
